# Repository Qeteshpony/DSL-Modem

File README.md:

# DSL-Modem Controller

A project to control a certain DSL-Modem through its internal serial port with a Raspberry Pi

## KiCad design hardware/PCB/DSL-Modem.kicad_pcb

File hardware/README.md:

# Hardware Parts
### PCB
The KiCad Files for the board that connects the Raspberry Pi to the rest of the hardware

### STL-Files
The front- and backpanels I created to mount the hardware into a 19" "Splice Box" case

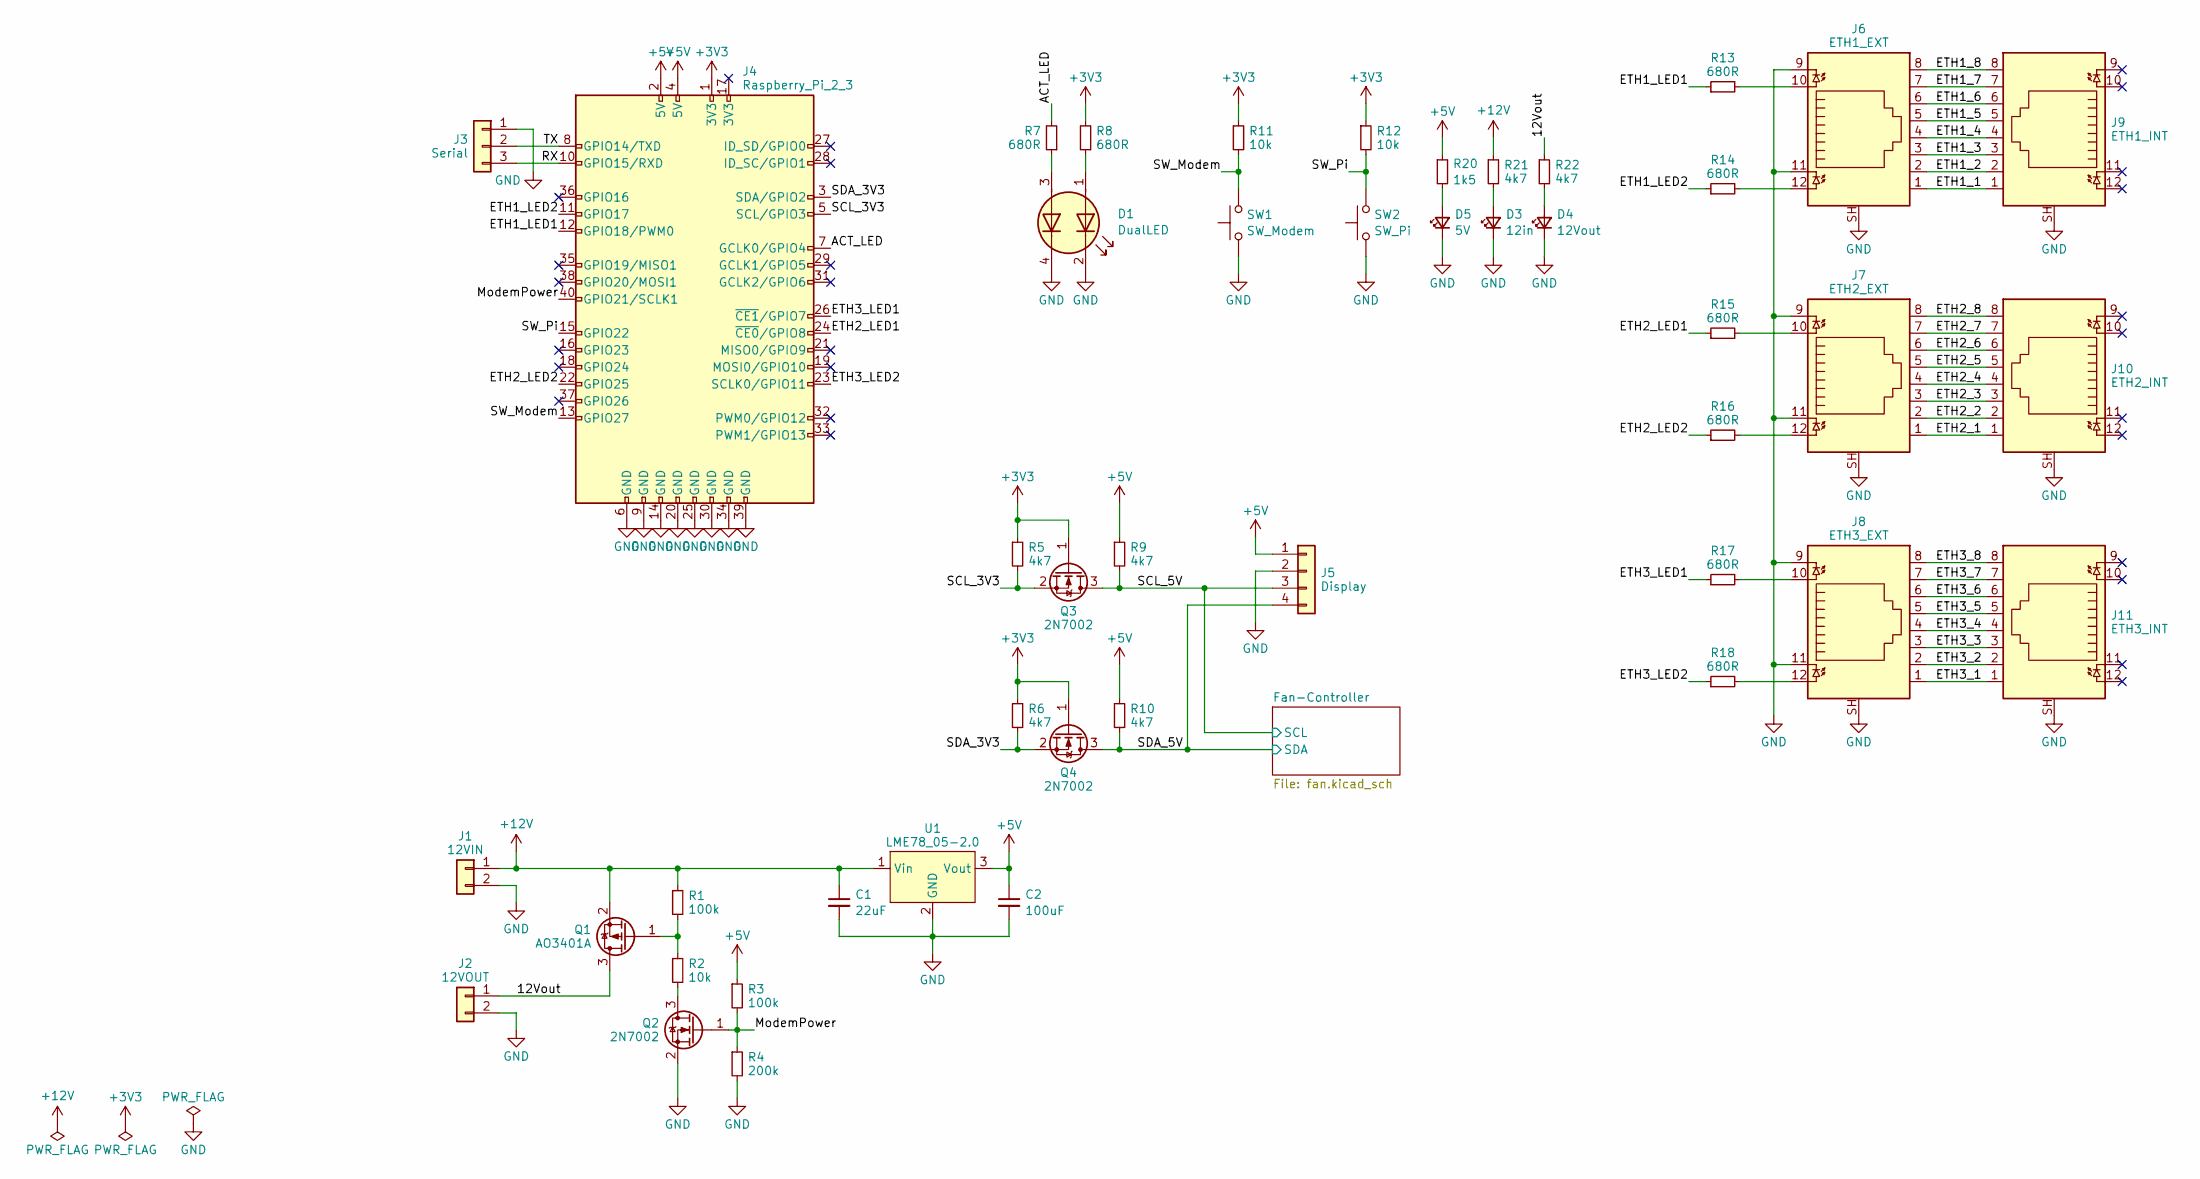
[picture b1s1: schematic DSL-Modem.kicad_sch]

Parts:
C1: 22uF; C_0805_2012Metric; LCSC C45783
C2: 100uF; C_1206_3216Metric; LCSC C15008
D1: DualLED; Everlight_Dual_LED_2x3mm
D3: 12in; LED_0603_1608Metric; LCSC C2286
D4: 12Vout; LED_0603_1608Metric; LCSC C2286
D5: 5V; LED_0603_1608Metric; LCSC C2286
J1: 12VIN; CTB9352-2
J2: 12VOUT; CTB9352-2
J3: Serial; PinHeader_1x03_P2.54mm_Vertical
J4: Raspberry_Pi_2_3; Raspberry Pi Universal Footprint
J5: Display; PinHeader_1x04_P2.54mm_Vertical
J6: ETH1_EXT; RJ45C5_R1D_3.2E4G-Y_RL
J7: ETH2_EXT; RJ45C5_R1D_3.2E4G-Y_RL
J8: ETH3_EXT; RJ45C5_R1D_3.2E4G-Y_RL
J9: ETH1_INT; RJ45C5_R1D_3.2E4G-Y_RL
J10: ETH2_INT; RJ45C5_R1D_3.2E4G-Y_RL
J11: ETH3_INT; RJ45C5_R1D_3.2E4G-Y_RL
Q1: AO3401A; SOT-23; LCSC C15127
Q2, Q3, Q4: 2N7002; SOT-23; LCSC C8545
R1, R3: 100k; R_0603_1608Metric; LCSC C25803
R2, R11, R12: 10k; R_0603_1608Metric; LCSC C25804
R4: 200k; R_0603_1608Metric; LCSC C25811
R5, R6, R9, R10, R21, R22: 4k7; R_0603_1608Metric; LCSC C23162
R7, R8, R13, R14, R15, R16, R17, R18: 680R; R_0603_1608Metric; LCSC C23228
R20: 1k5; R_0603_1608Metric; LCSC C22843
SW1: SW_Modem; SW_Tactile_SPST_Angled_PTS645Vx83-2LFS
SW2: SW_Pi; SW_Tactile_SPST_Angled_PTS645Vx83-2LFS
U1: LME78_05-2.0; LME78_1.0-Series

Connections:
+3V3: J4.1 (3V3), Q3.1 (G), Q4.1 (G), R5.1, R6.1, R8.2, R11.1, R12.1
+12V: C1.1, J1.1, Q1.2 (S), R1.1, R21.1, U1.1 (Vin); also elsewhere on the board
/12Vout: J2.1, Q1.3 (D), R22.1
/ACT_LED: J4.7 (GCLK0/GPIO4), R7.2
/ETH1_1: J6.1, J9.1
/ETH1_2: J6.2, J9.2
/ETH1_3: J6.3, J9.3
/ETH1_4: J6.4, J9.4
/ETH1_5: J6.5, J9.5
/ETH1_6: J6.6, J9.6
/ETH1_7: J6.7, J9.7
/ETH1_8: J6.8, J9.8
/ETH1_LED1: J4.12 (GPIO18/PWM0), R13.1
/ETH1_LED2: J4.11 (GPIO17), R14.1
/ETH2_1: J7.1, J10.1
/ETH2_2: J7.2, J10.2
/ETH2_3: J7.3, J10.3
/ETH2_4: J7.4, J10.4
/ETH2_5: J7.5, J10.5
/ETH2_6: J7.6, J10.6
/ETH2_7: J7.7, J10.7
/ETH2_8: J7.8, J10.8
/ETH2_LED1: J4.24 (~CE0/GPIO8), R15.1
/ETH2_LED2: J4.22 (GPIO25), R16.1
/ETH3_1: J8.1, J11.1
/ETH3_2: J8.2, J11.2
/ETH3_3: J8.3, J11.3
/ETH3_4: J8.4, J11.4
/ETH3_5: J8.5, J11.5
/ETH3_6: J8.6, J11.6
/ETH3_7: J8.7, J11.7
/ETH3_8: J8.8, J11.8
/ETH3_LED1: J4.26 (~CE1/GPIO7), R17.1
/ETH3_LED2: J4.23 (SCLK0/GPIO11), R18.1
/ModemPower: J4.40 (GPIO21/SCLK1), Q2.1 (G), R3.2, R4.1
/RX: J3.3, J4.10 (GPIO15/RXD)
/SCL_3V3: J4.5 (SCL/GPIO3), Q3.2 (S), R5.2
/SCL_5V: J5.3, Q3.3 (D), R9.2; also elsewhere on the board
/SDA_3V3: J4.3 (SDA/GPIO2), Q4.2 (S), R6.2
/SDA_5V: J5.4, Q4.3 (D), R10.2; also elsewhere on the board
/SW_Modem: J4.13 (GPIO27), R11.2, SW1.2
/SW_Pi: J4.15 (GPIO22), R12.2, SW2.2
/TX: J3.2, J4.8 (GPIO14/TXD)
unnamed: D1.1 (A1), R8.1
unnamed: D1.3 (A2), R7.1
unnamed: D3.2 (A), R21.2
unnamed: D4.2 (A), R22.2
unnamed: D5.2 (A), R20.2
unnamed: J6.10, R13.2
unnamed: J6.12, R14.2
unnamed: J7.10, R15.2
unnamed: J7.12, R16.2
unnamed: J8.10, R17.2
unnamed: J8.12, R18.2
unnamed: Q1.1 (G), R1.2, R2.1
unnamed: Q2.3 (D), R2.2

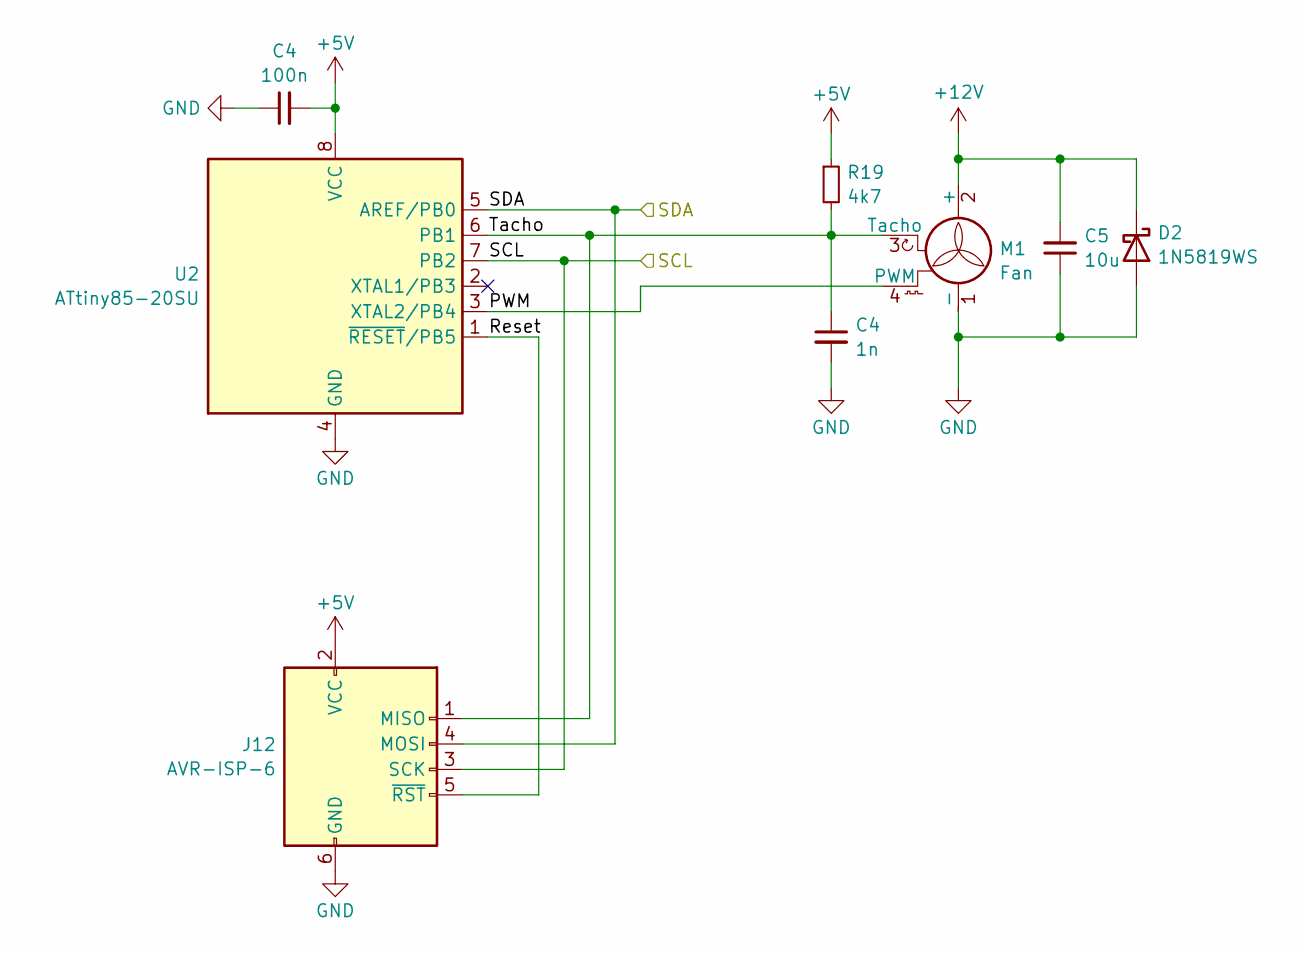
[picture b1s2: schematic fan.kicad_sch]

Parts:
C4: 1n; C_0603_1608Metric; LCSC C1588
C5: 10u; C_0603_1608Metric; LCSC C96446
D2: 1N5819WS; D_SOD-323; LCSC C191023
J12: AVR-ISP-6; PinHeader_2x03_P2.54mm_Vertical
M1: Fan; FanPinHeader_1x04_P2.54mm_Vertical
R19: 4k7; R_0603_1608Metric; LCSC C23162
U2: ATtiny85-20SU; SOIC-8W_5.3x5.3mm_P1.27mm

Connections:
+12V: C5.2, D2.1 (K), M1.2 (+); also elsewhere on the board
/Fan-Controller/PWM: M1.4 (PWM), U2.3 (XTAL2/PB4)
/Fan-Controller/Reset: J12.5 (~RST), U2.1 (~RESET/PB5)
/SCL_5V: J12.3 (SCK), U2.7 (PB2); also elsewhere on the board
/SDA_5V: J12.4 (MOSI), U2.5 (AREF/PB0); also elsewhere on the board

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
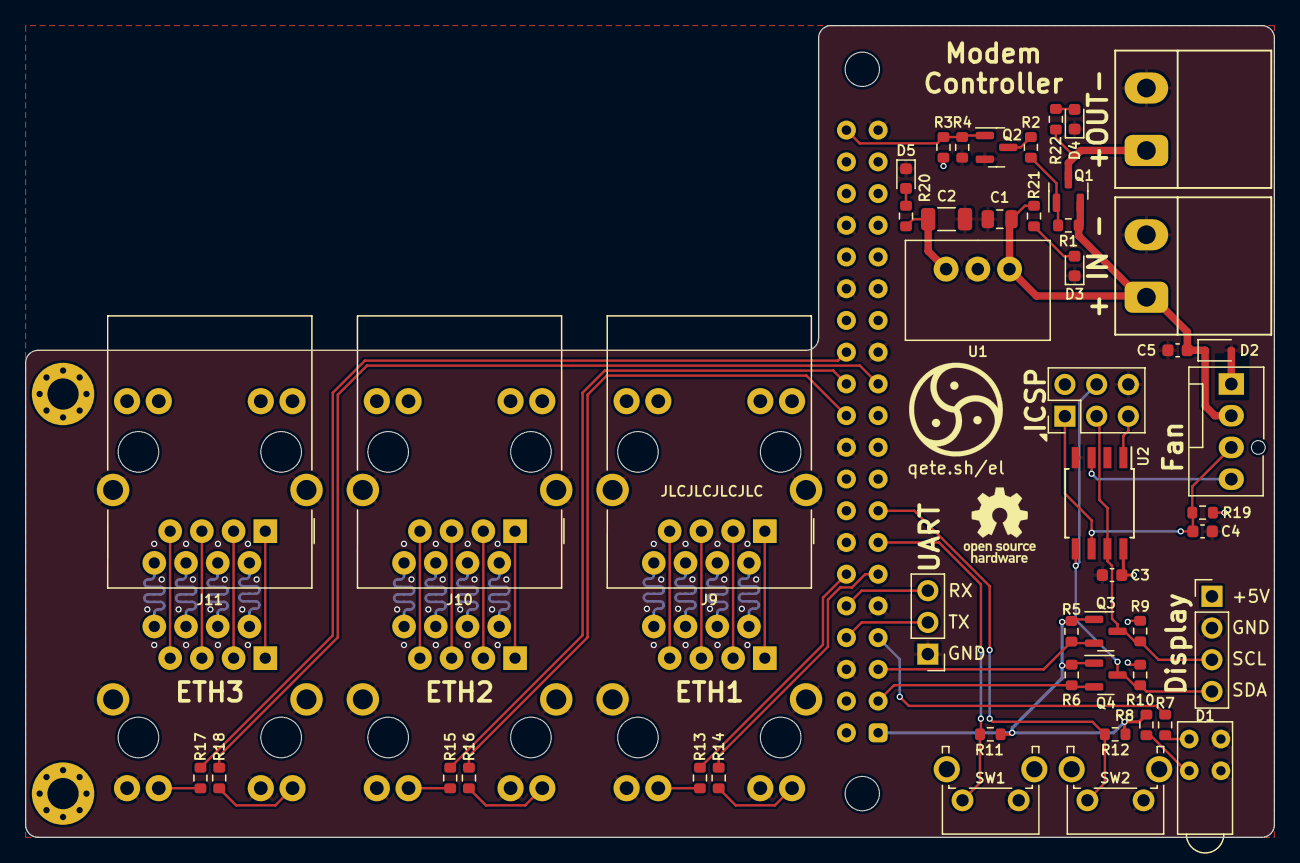
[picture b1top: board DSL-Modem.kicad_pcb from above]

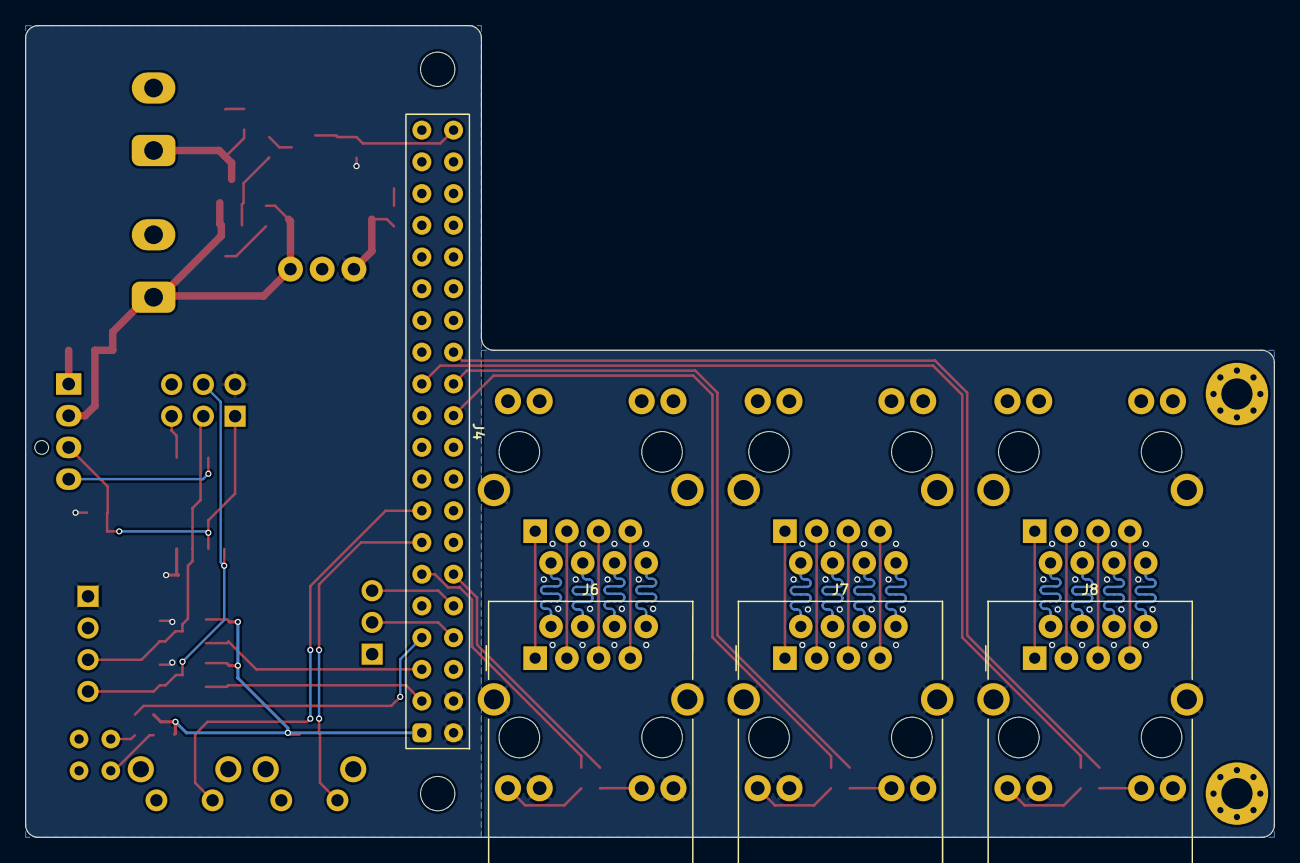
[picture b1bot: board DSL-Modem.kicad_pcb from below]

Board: 2 copper layers, 100.0 x 65.0 mm, 53 parts (3 on the bottom side), 61 nets.

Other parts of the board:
C3: 100n; C_0603_1608Metric

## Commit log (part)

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2023-10-17 feat: initial commit
2023-10-17 docs: create LICENSE
2023-10-17 docs: add licensing information
2023-10-18 fix: automatic restart of mqtt client
2023-10-18 feat: add hardware sources
2023-10-20 fix: automatic recovery from wrong prompt
2023-11-03 fix: change restart interval in case of failure
2023-11-03 fix: add try-block in case of connection problems
2024-01-26 fix: retain MQTT messages for sensor data
2024-06-22 fix: add working directory
2024-07-17 fix: catch more exceptions
    Since communication with the modem is sometimes unreliable we need to catch more exceptions
2024-08-12 feat: write values to files
2024-08-27 style: typo
2025-11-01 fix: try to fix occasional hangs in serial connection
